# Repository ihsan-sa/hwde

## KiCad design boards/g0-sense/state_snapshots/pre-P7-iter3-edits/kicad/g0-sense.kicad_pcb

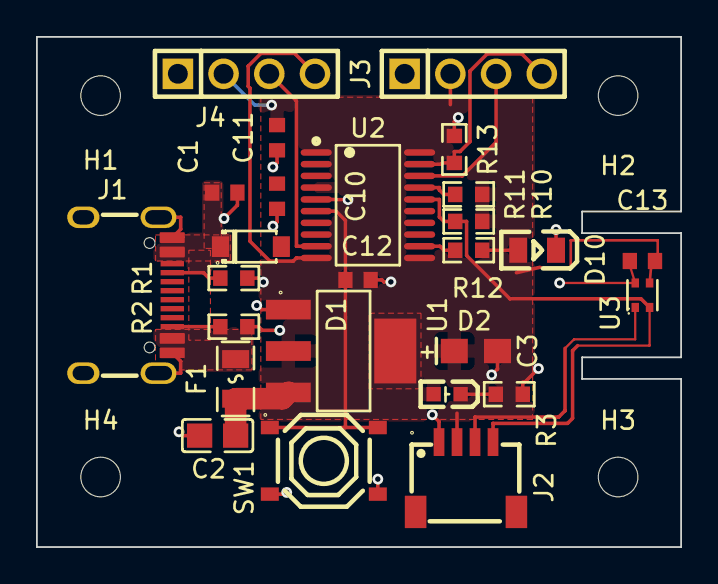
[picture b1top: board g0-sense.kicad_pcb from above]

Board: 2 copper layers, 35.8 x 28.3 mm, 30 parts (0 on the bottom side), 16 nets.

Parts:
C1, C10, C12, C13: 100nF 50V X7R; C0603
C2: 10uF 25V X5R; C0805
C3: 22uF 10V tantalum; CASE-A_3216
C11: 4.7uF 16V X5R; C0603
D1: SMF5.0A TVS 5V; SOD-123_L2.8-W1.8-LS3.7-RD
D2: Red LED; LED-SMD_L1.6-W0.8-R-RD
D10: Green 0805; LED0805-R-RD
F1: PTC 750mA 16V; F0805
H1, H2, H3, H4: MountingHole_2.2mm_M2
J1: TYPE-C-31-M-12; USB-C_SMD-TYPE-C-31-M-12_1
J2: Qwiic JST SH 4P; CONN-SMD_4P-P1.00_SM04B-SRSS-TB-LF-SN
J3, J4: 1x4 2.54mm THT (DNP); HDR-TH_4P-P2.54-V-M
R1, R2: 5.1k 1%; R0603
R3: 680R 1%; R0603
R10, R11: 1.5k; R0603
R12: 100R; R0603
R13: 10k; R0603
SW1: Tactile button; SW-SMD_4P-L5.1-W5.1-P3.70-LS6.5-TL_H1.5
U1: AMS1117-3.3; SOT-223-3_L6.5-W3.4-P2.30-LS7.0-BR
U2: STM32G030F6P6; TSSOP-20_L6.5-W4.4-P0.65-LS6.4-BL
U3: SHT40-AD1B-R2; DFN-4_L1.5-W1.5-P0.8-TL-EP

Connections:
+3V3: C3.1, C10.1, C11.1, C13.1, D2.1, J2.2, J3.2, J4.2, R10.2, R11.2, U1.2, U1.4, U2.4, U3.3
+5V: C2.1, F1.2, U1.3
/main/LED_A: D10.1, R12.2
/main/LED_USER: R12.1, U2.12
/main/NRST: C12.1, SW1.1, SW1.2, U2.6
/main/SCL: J2.4, R11.1, U2.16, U3.2
/main/SDA: J2.3, R10.1, U2.17, U3.1
/main/SWCLK: J3.4, R13.1, U2.19
/main/SWDIO: J3.3, U2.18
/main/UART_RX: J4.4, U2.10
/main/UART_TX: J4.3, U2.9
/power/CC1: J1.A5, R1.1
/power/CC2: J1.B5, R2.1
/power/PWR_LED_K: D2.2, R3.1
GND: C1.2, C2.2, C3.2, C10.2, C11.2, C12.2, C13.2, D1.2, D10.2, J1.1, J1.2, J1.3, J1.4, J1.A1B12, J1.B1A12, J2.1, J3.1, J4.1, R1.2, R2.2, R3.2, R13.2, SW1.3, SW1.4, U1.1, U2.5, U3.4
VBUS: C1.1, D1.1, F1.1, J1.A4B9, J1.B4A9

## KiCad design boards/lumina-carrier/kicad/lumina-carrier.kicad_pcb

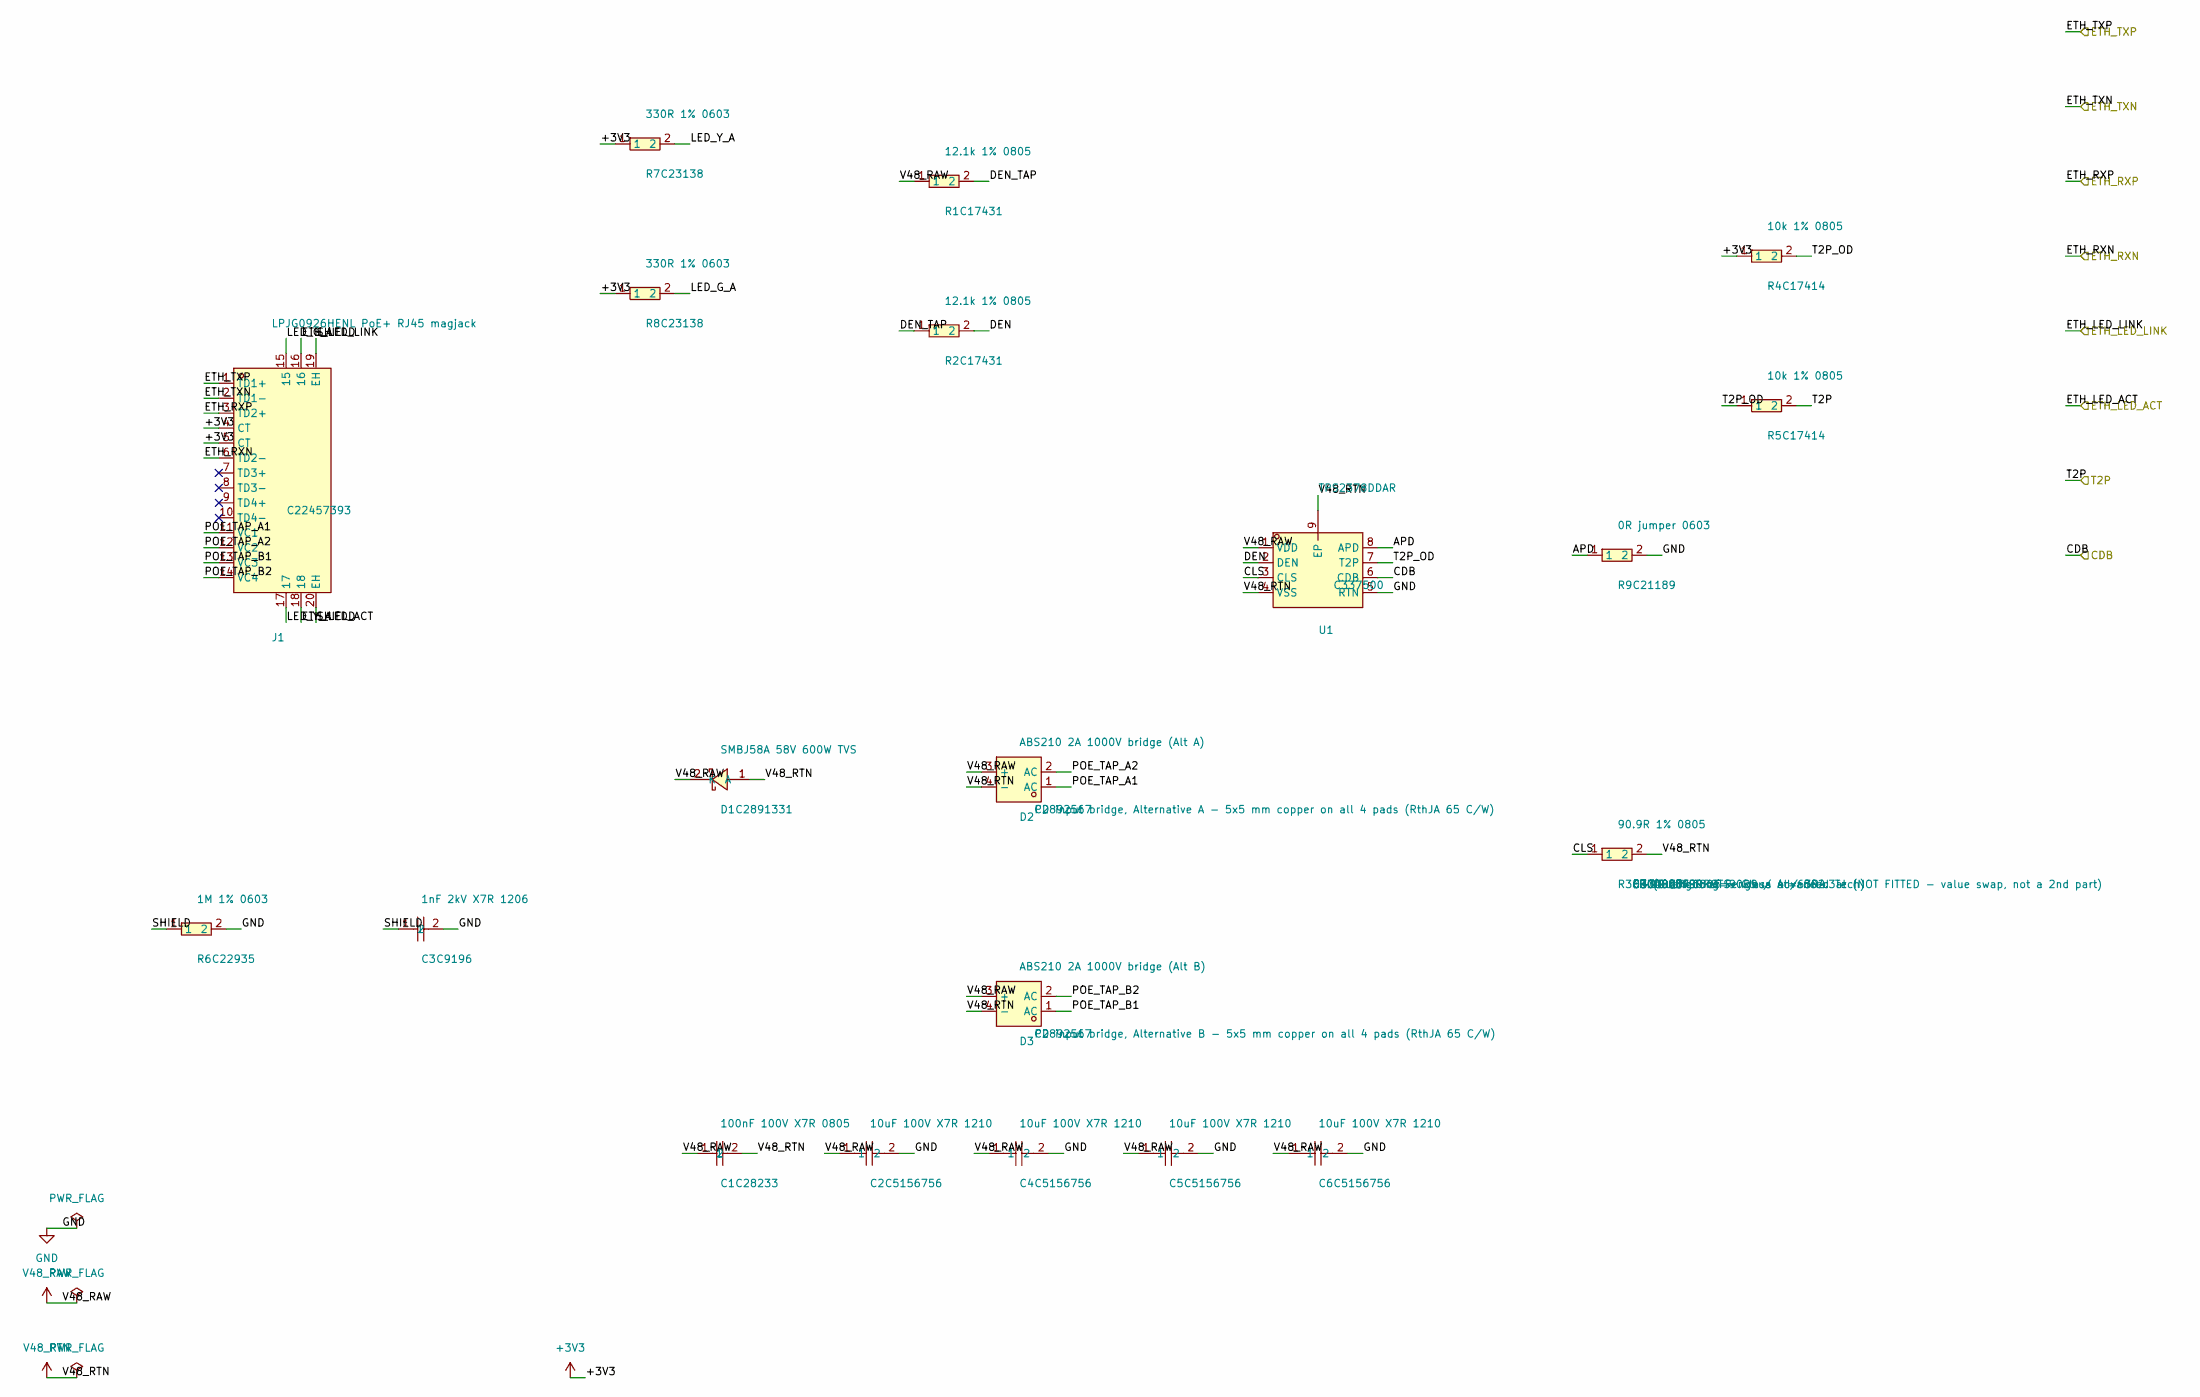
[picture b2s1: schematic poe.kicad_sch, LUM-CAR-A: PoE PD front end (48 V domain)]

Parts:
C1: 100nF 100V X7R 0805; C0805; LCSC C28233
C2, C4, C5, C6: 10uF 100V X7R 1210; C1210; LCSC C5156756
C3: 1nF 2kV X7R 1206; C1206; LCSC C9196
D1: SMBJ58A 58V 600W TVS; SMB_L4.3-W3.6-LS5.4-R-RD; LCSC C2891331
D2: ABS210 2A 1000V bridge (Alt A); ABF_L5.1-W4.4-P4.00-LS6.2-BL; LCSC C2892567
D3: ABS210 2A 1000V bridge (Alt B); ABF_L5.1-W4.4-P4.00-LS6.2-BL; LCSC C2892567
J1: LPJG0926HENL PoE+ RJ45 magjack; RJ45-TH_LPJG0926HENL_C22457393; LCSC C22457393
R1, R2: 12.1k 1% 0805; R0805; LCSC C17431
R3: 90.9R 1% 0805; R0805; MPN FRC0805F90R9TS; LCSC C3000584
R4, R5: 10k 1% 0805; R0805; LCSC C17414
R6: 1M 1% 0603; R0603; LCSC C22935
R7, R8: 330R 1% 0603; R0603; LCSC C23138
R9: 0R jumper 0603; R0603; LCSC C21189
U1: TPS2378DDAR; SOIC-8-1EP_3.9x4.9mm_P1.27mm_EP2.95x4.9mm_Mask2.71x3.4mm; LCSC C337500

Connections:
+3V3: J1.4 (CT), J1.5 (CT), R4.1, R7.1, R8.1; also elsewhere on the board
/CDB: U1.6 (CDB); also elsewhere on the board
/ETH_LED_ACT: J1.18; also elsewhere on the board
/ETH_LED_LINK: J1.16; also elsewhere on the board
/ETH_RXN: J1.6 (TD2-); also elsewhere on the board
/ETH_RXP: J1.3 (TD2+); also elsewhere on the board
/ETH_TXN: J1.2 (TD1-); also elsewhere on the board
/ETH_TXP: J1.1 (TD1+); also elsewhere on the board
/T2P: R5.2; also elsewhere on the board
/poe/APD: R9.1, U1.8 (APD)
/poe/CLS: R3.1, U1.3 (CLS)
/poe/DEN: R2.2, U1.2 (DEN)
/poe/DEN_TAP: R1.2, R2.1
/poe/LED_G_A: J1.15, R8.2
/poe/LED_Y_A: J1.17, R7.2
/poe/POE_TAP_A1: D2.1 (AC), J1.11 (VC1)
/poe/POE_TAP_A2: D2.2 (AC), J1.12 (VC2)
/poe/POE_TAP_B1: D3.1 (AC), J1.13 (VC3)
/poe/POE_TAP_B2: D3.2 (AC), J1.14 (VC4)
/poe/SHIELD: C3.1, J1.19 (EH), J1.20 (EH), R6.1
/poe/T2P_OD: R4.2, R5.1, U1.7 (T2P)
GND: C2.2, C3.2, C4.2, C5.2, C6.2, R6.2, R9.2, U1.5 (RTN); also elsewhere on the board
V48_RAW: C1.1, C2.1, C4.1, C5.1, C6.1, D1.2 (K), D2.3 (+), D3.3 (+), R1.1, U1.1 (VDD); also elsewhere on the board
V48_RTN: C1.2, D1.1 (A), D2.4 (-), D3.4 (-), R3.2, U1.4 (VSS), U1.9 (EP)

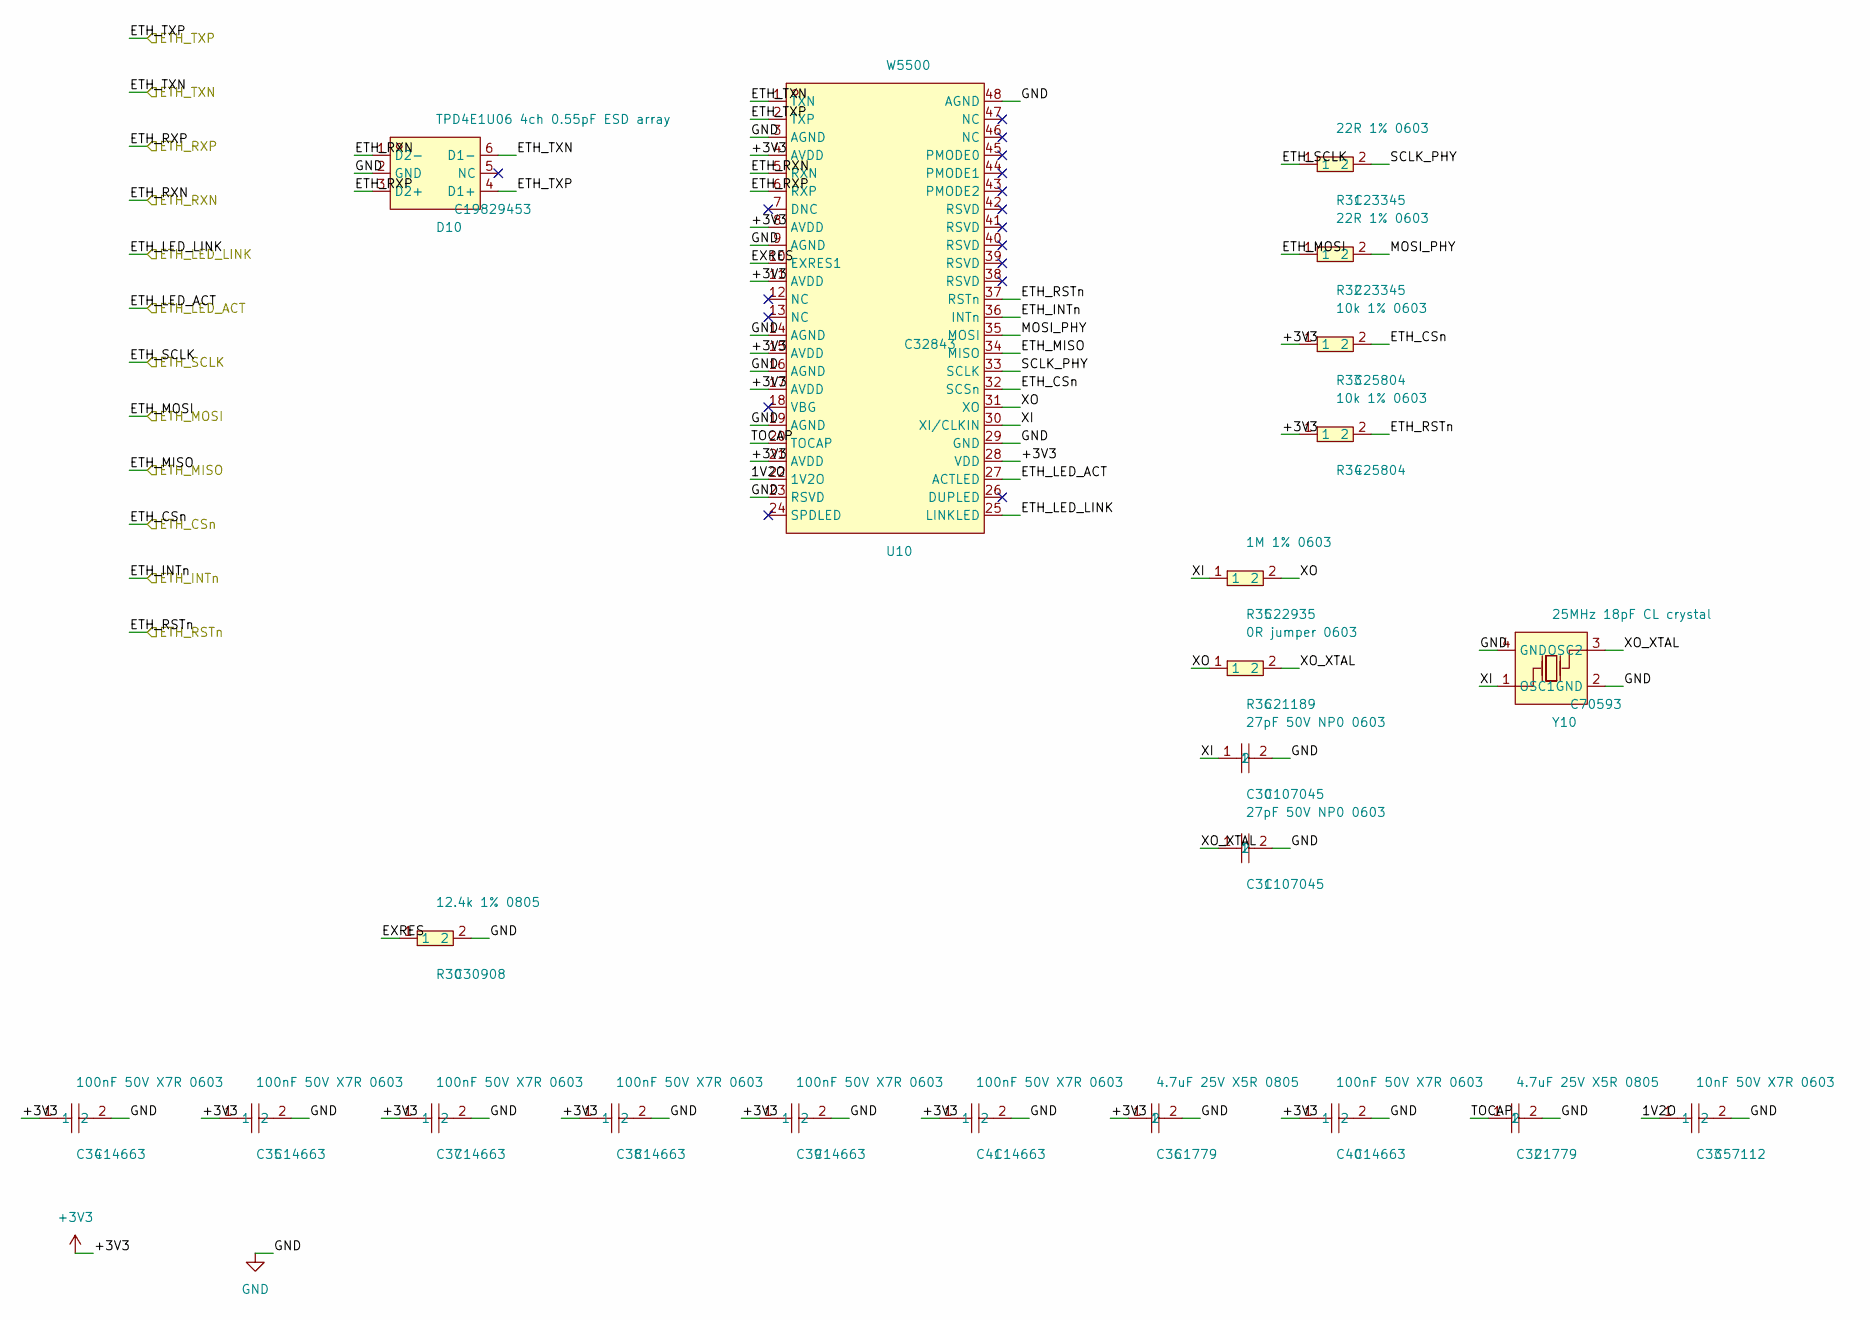
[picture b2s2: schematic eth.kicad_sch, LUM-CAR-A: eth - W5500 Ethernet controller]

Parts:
C30, C31: 27pF 50V NP0 0603; C0603; LCSC C107045
C32, C36: 4.7uF 25V X5R 0805; C0805; LCSC C1779
C33: 10nF 50V X7R 0603; C0603; LCSC C57112
C34, C35, C37, C38, C39, C40, C41: 100nF 50V X7R 0603; C0603; LCSC C14663
D10: TPD4E1U06 4ch 0.55pF ESD array; SOT-23-6_L2.9-W1.6-P0.95-LS2.8-BR; LCSC C19829453
R30: 12.4k 1% 0805; R0805; LCSC C30908
R31, R32: 22R 1% 0603; R0603; LCSC C23345
R33, R34: 10k 1% 0603; R0603; LCSC C25804
R35: 1M 1% 0603; R0603; LCSC C22935
R36: 0R jumper 0603; R0603; LCSC C21189
U10: W5500; LQFP-48_L7.0-W7.0-P0.50-LS9.0-BL; LCSC C32843
Y10: 25MHz 18pF CL crystal; OSC-SMD_4P-L3.2-W2.5-BL_SIT8008BI; LCSC C70593

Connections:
+3V3: C34.1, C35.1, C36.1, C37.1, C38.1, C39.1, C40.1, C41.1, R33.1, R34.1, U10.4 (AVDD), U10.8 (AVDD), U10.11 (AVDD), U10.15 (AVDD), U10.17 (AVDD), U10.21 (AVDD), U10.28 (VDD); also elsewhere on the board
/ETH_CSn: R33.2, U10.32 (SCSn); also elsewhere on the board
/ETH_INTn: U10.36 (INTn); also elsewhere on the board
/ETH_LED_ACT: U10.27 (ACTLED); also elsewhere on the board
/ETH_LED_LINK: U10.25 (LINKLED); also elsewhere on the board
/ETH_MISO: U10.34 (MISO); also elsewhere on the board
/ETH_MOSI: R32.1; also elsewhere on the board
/ETH_RSTn: R34.2, U10.37 (RSTn); also elsewhere on the board
/ETH_RXN: D10.1 (D2-), U10.5 (RXN); also elsewhere on the board
/ETH_RXP: D10.3 (D2+), U10.6 (RXP); also elsewhere on the board
/ETH_SCLK: R31.1; also elsewhere on the board
/ETH_TXN: D10.6 (D1-), U10.1 (TXN); also elsewhere on the board
/ETH_TXP: D10.4 (D1+), U10.2 (TXP); also elsewhere on the board
/eth/1V2O: C33.1, U10.22 (1V2O)
/eth/EXRES: R30.1, U10.10 (EXRES1)
/eth/MOSI_PHY: R32.2, U10.35 (MOSI)
/eth/SCLK_PHY: R31.2, U10.33 (SCLK)
/eth/TOCAP: C32.1, U10.20 (TOCAP)
/eth/XI: C30.1, R35.1, U10.30 (XI/CLKIN), Y10.1 (OSC1)
/eth/XO: R35.2, R36.1, U10.31 (XO)
/eth/XO_XTAL: C31.1, R36.2, Y10.3 (OSC2)
GND: C30.2, C31.2, C32.2, C33.2, C34.2, C35.2, C36.2, C37.2, C38.2, C39.2, C40.2, C41.2, D10.2 (GND), R30.2, U10.3 (AGND), U10.9 (AGND), U10.14 (AGND), U10.16 (AGND), U10.19 (AGND), U10.23 (RSVD), U10.29 (GND), U10.48 (AGND), Y10.2 (GND), Y10.4 (GND); also elsewhere on the board

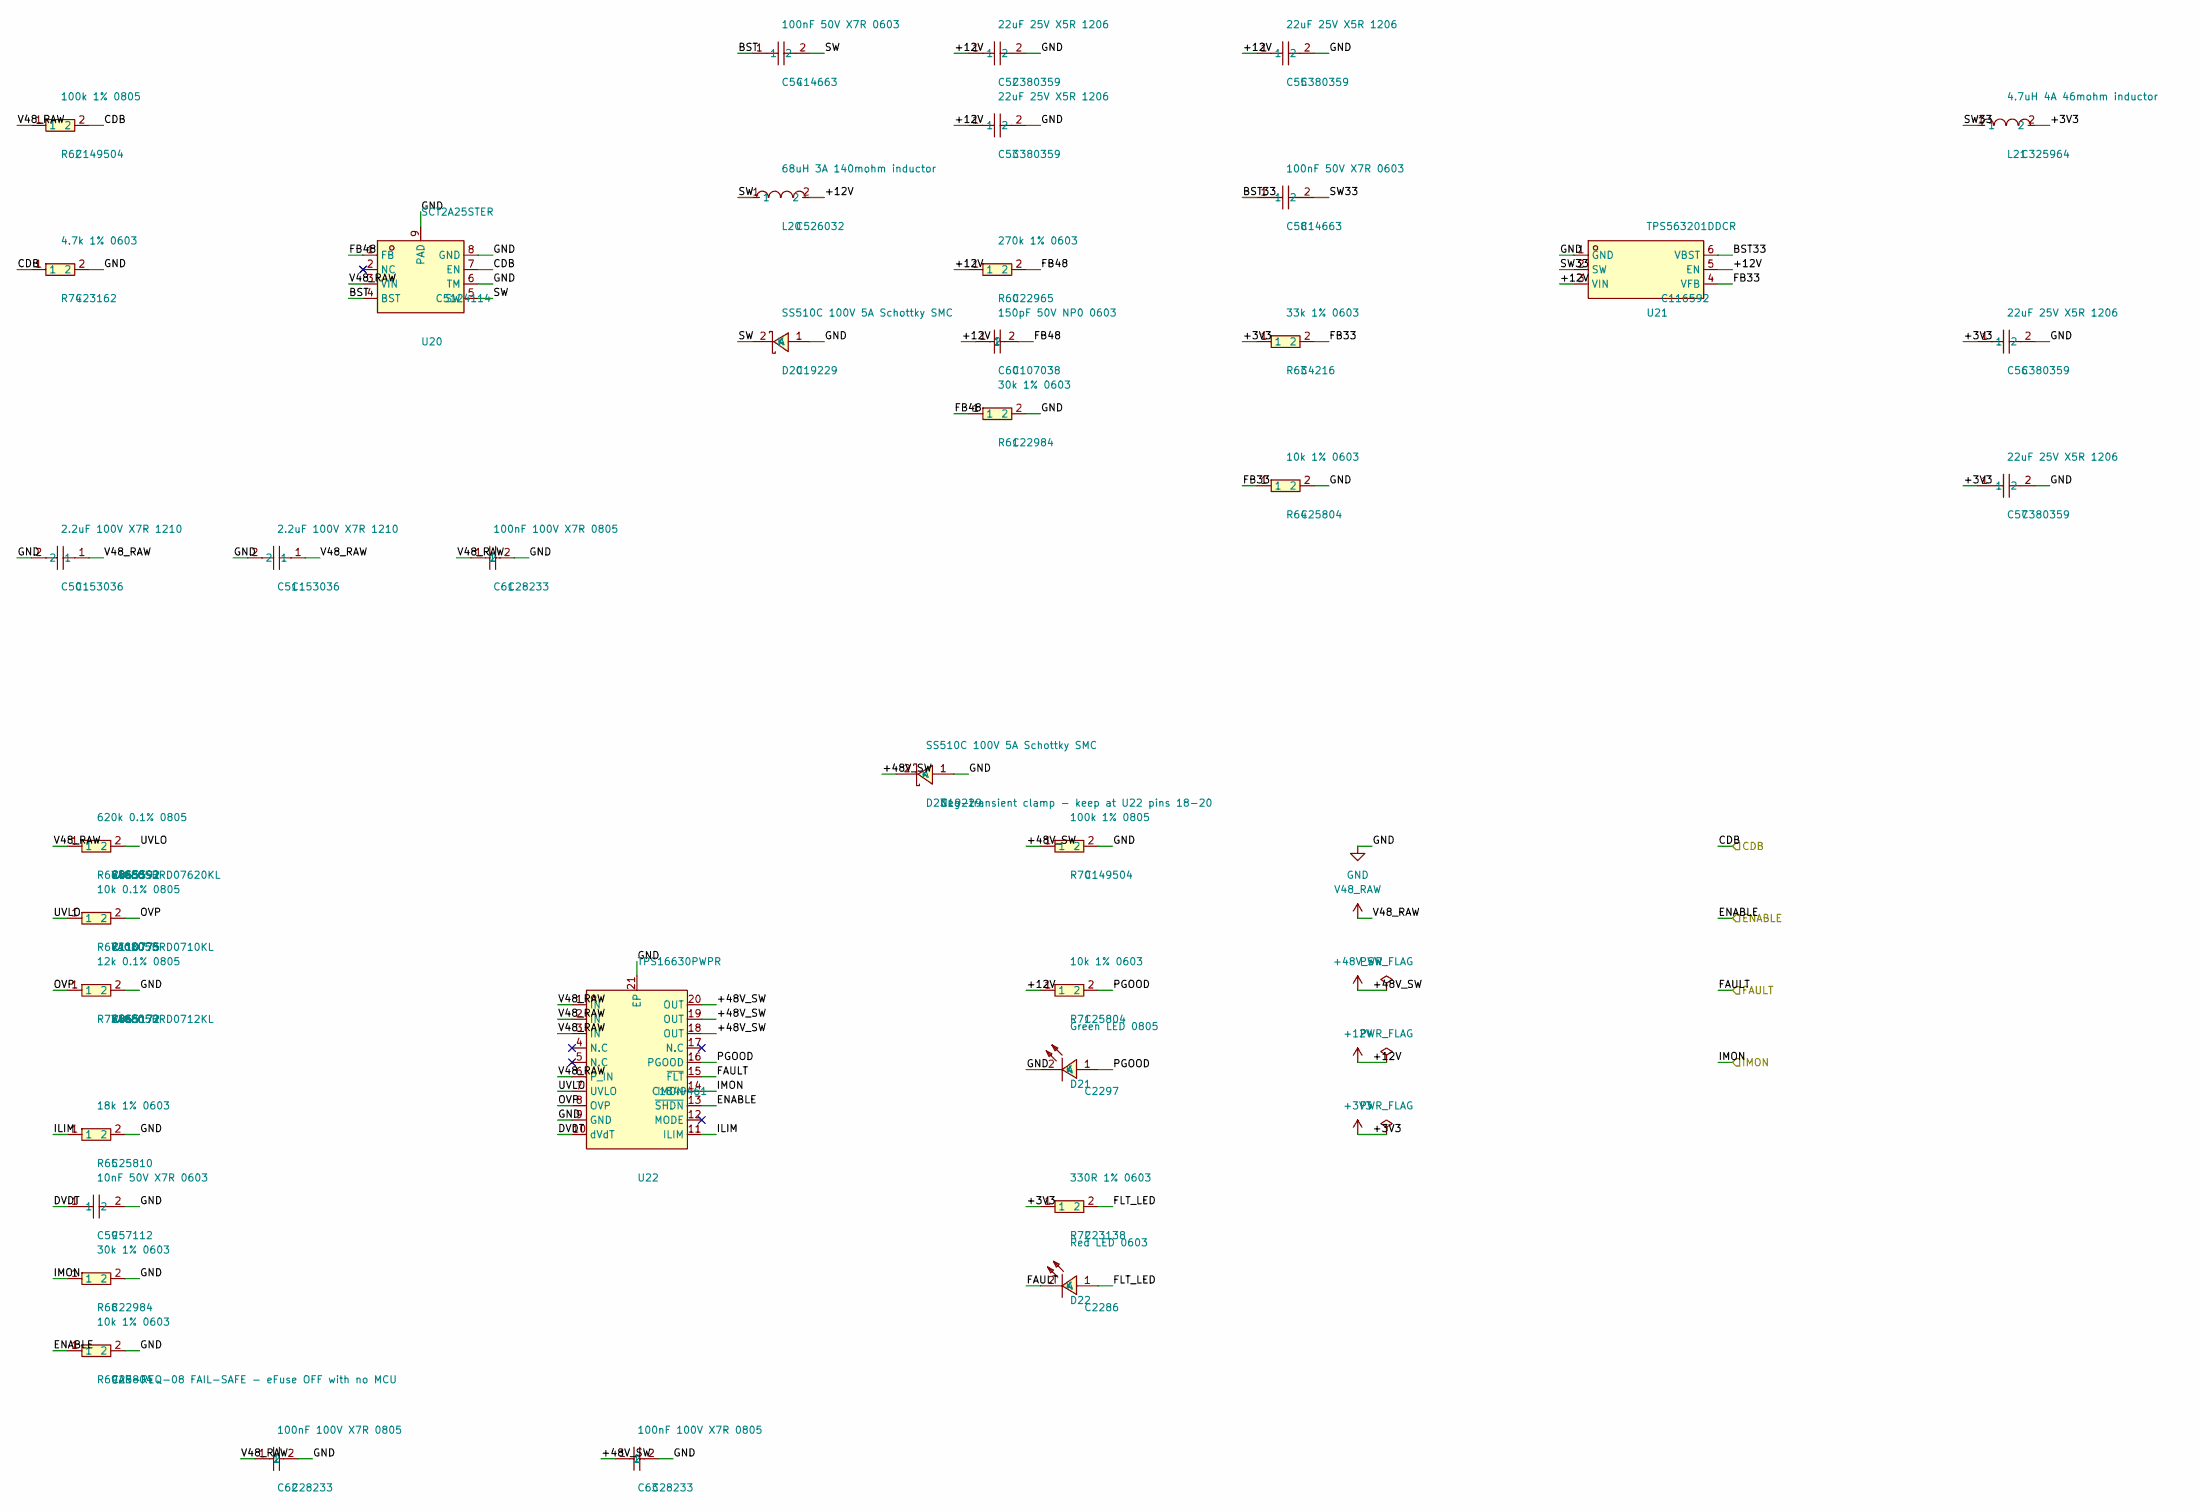
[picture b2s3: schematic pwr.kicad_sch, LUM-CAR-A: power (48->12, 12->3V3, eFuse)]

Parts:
C50, C51: 2.2uF 100V X7R 1210; C1210; LCSC C153036
C52, C53, C55, C56, C57: 22uF 25V X5R 1206; C1206; LCSC C380359
C54, C58: 100nF 50V X7R 0603; C0603; LCSC C14663
C59: 10nF 50V X7R 0603; C0603; LCSC C57112
C60: 150pF 50V NP0 0603; C0603; LCSC C107038
C61, C62, C63: 100nF 100V X7R 0805; C0805; LCSC C28233
D20, D23: SS510C 100V 5A Schottky SMC; SMC_L7.1-W6.2-LS8.1-R-RD; LCSC C19229
D21: Green LED 0805; LED0805-R-RD; LCSC C2297
D22: Red LED 0603; LED-SMD_L1.6-W0.8-R-RD; LCSC C2286
L20: 68uH 3A 140mohm inductor; IND-SMD_L12.6-W13.5; LCSC C526032
L21: 4.7uH 4A 46mohm inductor; IND-SMD_L5.4-W5.2; LCSC C325964
R60: 270k 1% 0603; R0603; LCSC C22965
R61, R68: 30k 1% 0603; R0603; LCSC C22984
R62, R70: 100k 1% 0805; R0805; LCSC C149504
R63: 33k 1% 0603; R0603; LCSC C4216
R64, R69, R71: 10k 1% 0603; R0603; LCSC C25804
R65: 18k 1% 0603; R0603; LCSC C25810
R66: 620k 0.1% 0805; R0805; MPN RT0805BRD07620KL; LCSC C865592
R67: 10k 0.1% 0805; R0805; MPN RT0805BRD0710KL; LCSC C110775
R72: 330R 1% 0603; R0603; LCSC C23138
R73: 12k 0.1% 0805; R0805; MPN RT0805BRD0712KL; LCSC C865172
R74: 4.7k 1% 0603; R0603; LCSC C23162
U20: SCT2A25STER; SOIC-8-1EP_3.9x4.9mm_P1.27mm_EP2.41x3.3mm; LCSC C5124114
U21: TPS563201DDCR; SOT-23-6_L2.9-W1.6-P0.95-LS2.8-BR; LCSC C116592
U22: TPS16630PWPR; HTSSOP-20-1EP_4.4x6.5mm_P0.65mm_EP3.4x6.5mm_Mask2.96x2.96mm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; LCSC C1849461

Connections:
+3V3: C56.1, C57.1, L21.2, R63.1, R72.1; also elsewhere on the board
+12V: C52.1, C53.1, C55.1, C60.1, L20.2, R60.1, R71.1, U21.3 (VIN), U21.5 (EN); also elsewhere on the board
+48V_SW: C63.1, D23.2 (K), R70.1, U22.18 (OUT), U22.19 (OUT), U22.20 (OUT); also elsewhere on the board
/CDB: R62.2, R74.1, U20.7 (EN); also elsewhere on the board
/ENABLE: R69.1, U22.13 (~SHDN); also elsewhere on the board
/FAULT: D22.2 (K), U22.15 (~FLT); also elsewhere on the board
/IMON: R68.1, U22.14 (IMON); also elsewhere on the board
/pwr/BST: C54.1, U20.4 (BST)
/pwr/BST33: C58.1, U21.6 (VBST)
/pwr/DVDT: C59.1, U22.10 (dVdT)
/pwr/FB33: R63.2, R64.1, U21.4 (VFB)
/pwr/FB48: C60.2, R60.2, R61.1, U20.1 (FB)
/pwr/FLT_LED: D22.1 (A), R72.2
/pwr/ILIM: R65.1, U22.11 (ILIM)
/pwr/OVP: R67.2, R73.1, U22.8 (OVP)
/pwr/PGOOD: D21.1 (A), R71.2, U22.16 (PGOOD)
/pwr/SW: C54.2, D20.2 (K), L20.1, U20.5 (SW)
/pwr/SW33: C58.2, L21.1, U21.2 (SW)
/pwr/UVLO: R66.2, R67.1, U22.7 (UVLO)
GND: C50.2, C51.2, C52.2, C53.2, C55.2, C56.2, C57.2, C59.2, C61.2, C62.2, C63.2, D20.1 (A), D21.2 (K), D23.1 (A), R61.2, R64.2, R65.2, R68.2, R69.2, R70.2, R73.2, R74.2, U20.6 (TM), U20.8 (GND), U20.9 (PAD), U21.1 (GND), U22.9 (GND), U22.21 (EP); also elsewhere on the board
V48_RAW: C50.1, C51.1, C61.1, C62.1, R62.1, R66.1, U20.3 (VIN), U22.1 (IN), U22.2 (IN), U22.3 (IN), U22.6 (P_IN); also elsewhere on the board

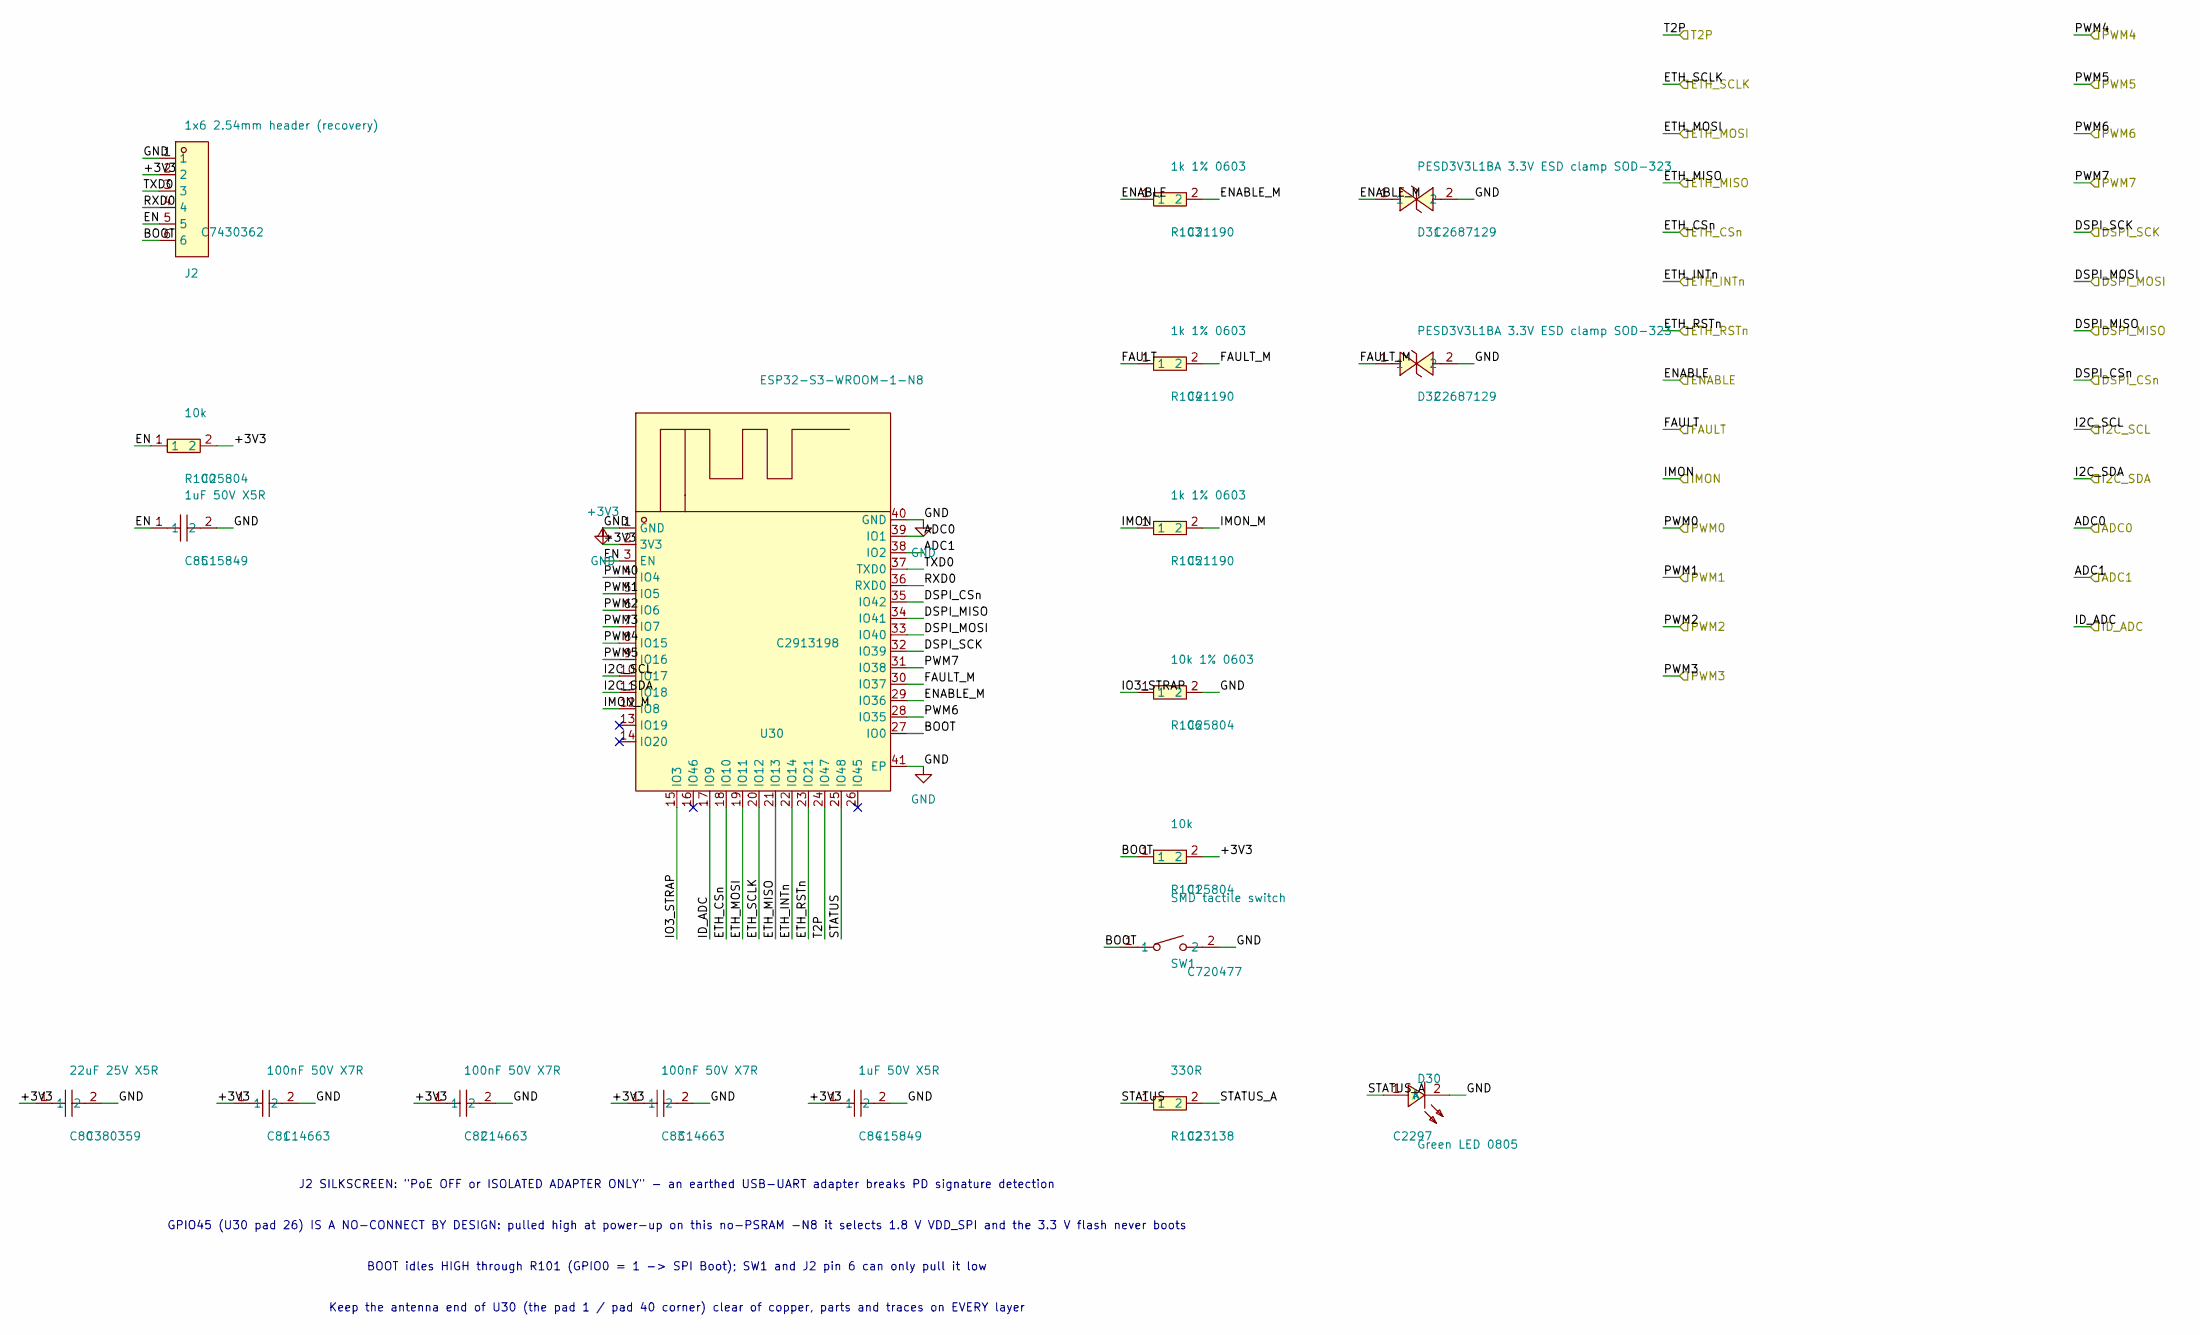
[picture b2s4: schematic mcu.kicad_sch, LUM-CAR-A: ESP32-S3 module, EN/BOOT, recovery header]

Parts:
C80: 22uF 25V X5R; C1206; LCSC C380359
C81, C82, C83: 100nF 50V X7R; C0603; LCSC C14663
C84, C85: 1uF 50V X5R; C0603; LCSC C15849
D30: Green LED 0805; LED0805-R-RD; LCSC C2297
D31, D32: PESD3V3L1BA 3.3V ESD clamp SOD-323; SOD-323_L1.7-W1.3-LS2.6-BI; LCSC C2687129
J2: 1x6 2.54mm header (recovery); CONN-TH_DS1021-1X6SF11-B; LCSC C7430362
R100, R101: 10k; R0603; LCSC C25804
R102: 330R; R0603; LCSC C23138
R103, R104, R105: 1k 1% 0603; R0603; LCSC C21190
R106: 10k 1% 0603; R0603; LCSC C25804
SW1: SMD tactile switch; SW-SMD_L3.9-W3.0-P4.45; LCSC C720477
U30: ESP32-S3-WROOM-1-N8; WIFIM-SMD_ESP32-S3-WROOM-1-N8; LCSC C2913198

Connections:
+3V3: C80.1, C81.1, C82.1, C83.1, C84.1, J2.2, R100.2, R101.2, U30.2 (3V3); also elsewhere on the board
/ADC0: U30.39 (IO1); also elsewhere on the board
/ADC1: U30.38 (IO2); also elsewhere on the board
/DSPI_CSn: U30.35 (IO42); also elsewhere on the board
/DSPI_MISO: U30.34 (IO41); also elsewhere on the board
/DSPI_MOSI: U30.33 (IO40); also elsewhere on the board
/DSPI_SCK: U30.32 (IO39); also elsewhere on the board
/ENABLE: R103.1; also elsewhere on the board
/ETH_CSn: U30.18 (IO10); also elsewhere on the board
/ETH_INTn: U30.22 (IO14); also elsewhere on the board
/ETH_MISO: U30.21 (IO13); also elsewhere on the board
/ETH_MOSI: U30.19 (IO11); also elsewhere on the board
/ETH_RSTn: U30.23 (IO21); also elsewhere on the board
/ETH_SCLK: U30.20 (IO12); also elsewhere on the board
/FAULT: R104.1; also elsewhere on the board
/I2C_SCL: U30.10 (IO17); also elsewhere on the board
/I2C_SDA: U30.11 (IO18); also elsewhere on the board
/ID_ADC: U30.17 (IO9); also elsewhere on the board
/IMON: R105.1; also elsewhere on the board
/PWM0: U30.4 (IO4); also elsewhere on the board
/PWM1: U30.5 (IO5); also elsewhere on the board
/PWM2: U30.6 (IO6); also elsewhere on the board
/PWM3: U30.7 (IO7); also elsewhere on the board
/PWM4: U30.8 (IO15); also elsewhere on the board
/PWM5: U30.9 (IO16); also elsewhere on the board
/PWM6: U30.28 (IO35); also elsewhere on the board
/PWM7: U30.31 (IO38); also elsewhere on the board
/T2P: U30.24 (IO47); also elsewhere on the board
/mcu/BOOT: J2.6, R101.1, SW1.1, U30.27 (IO0)
/mcu/EN: C85.1, J2.5, R100.1, U30.3 (EN)
/mcu/ENABLE_M: D31.1, R103.2, U30.29 (IO36)
/mcu/FAULT_M: D32.1, R104.2, U30.30 (IO37)
/mcu/IMON_M: R105.2, U30.12 (IO8)
/mcu/IO3_STRAP: R106.1, U30.15 (IO3)
/mcu/RXD0: J2.4, U30.36 (RXD0)
/mcu/STATUS: R102.1, U30.25 (IO48)
/mcu/STATUS_A: D30.1 (A), R102.2
/mcu/TXD0: J2.3, U30.37 (TXD0)
GND: C80.2, C81.2, C82.2, C83.2, C84.2, C85.2, D30.2 (K), D31.2, D32.2, J2.1, R106.2, SW1.2, U30.1 (GND), U30.40 (GND), U30.41 (EP); also elsewhere on the board

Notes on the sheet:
J2 SILKSCREEN: "PoE OFF or ISOLATED ADAPTER ONLY" - an earthed USB-UART adapter breaks PD signature detection
GPIO45 (U30 pad 26) IS A NO-CONNECT BY DESIGN: pulled high at power-up on this no-PSRAM -N8 it selects 1.8 V VDD_SPI and the 3.3 V flash never boots
BOOT idles HIGH through R101 (GPIO0 = 1 -> SPI Boot); SW1 and J2 pin 6 can only pull it low
Keep the antenna end of U30 (the pad 1 / pad 40 corner) clear of copper, parts and traces on EVERY layer

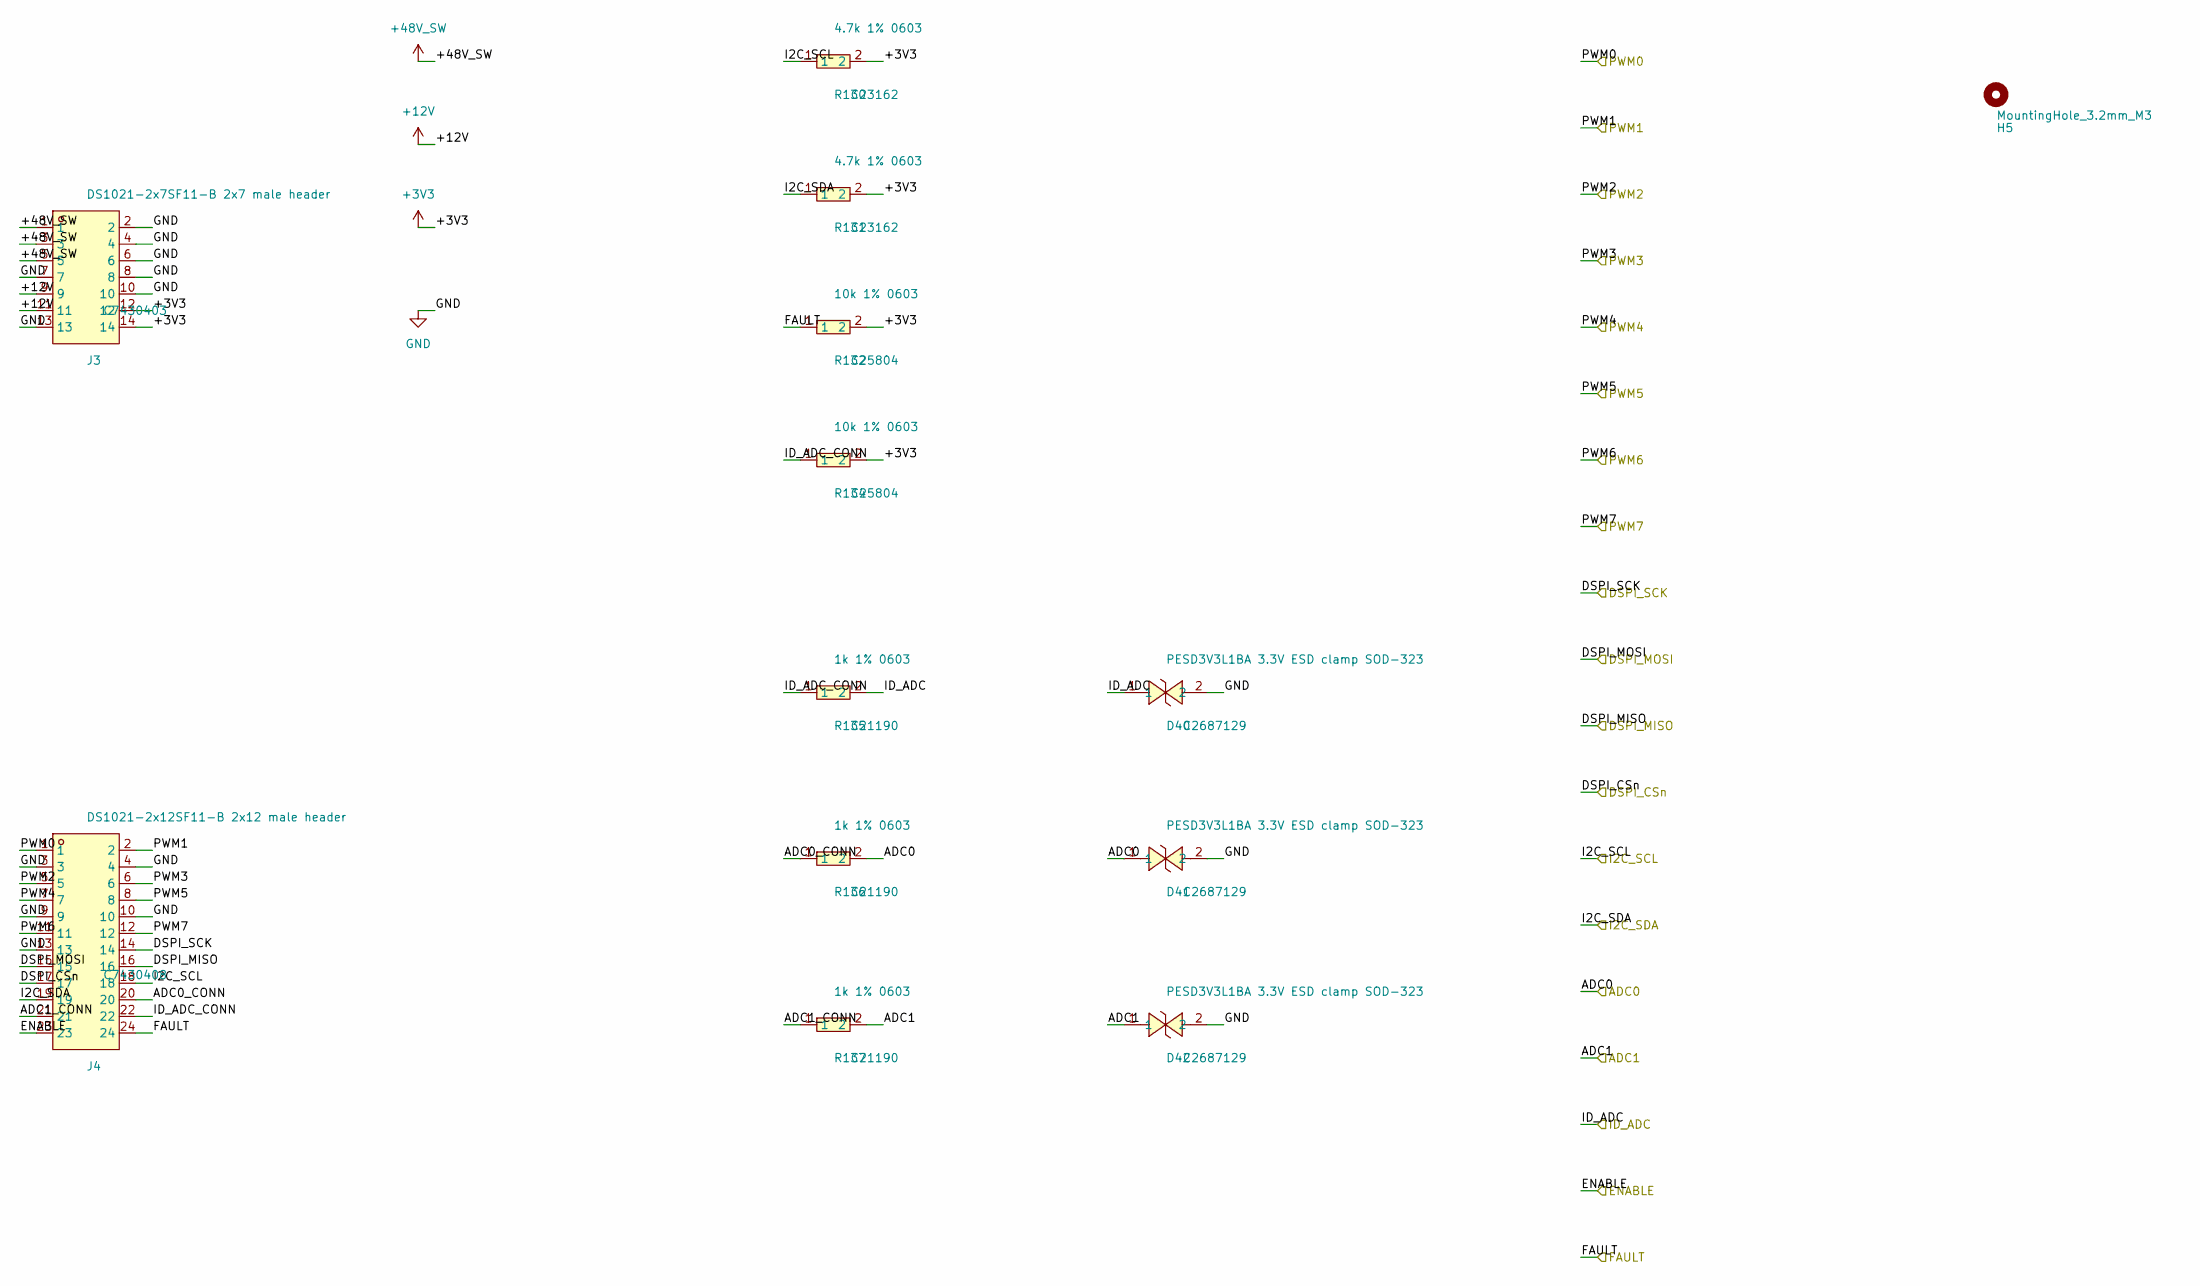
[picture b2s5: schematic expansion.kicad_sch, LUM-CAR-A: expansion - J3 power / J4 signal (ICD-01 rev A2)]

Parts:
D40, D41, D42: PESD3V3L1BA 3.3V ESD clamp SOD-323; SOD-323_L1.7-W1.3-LS2.6-BI; LCSC C2687129
H5: MountingHole_3.2mm_M3
J3: DS1021-2x7SF11-B 2x7 male header; HDR-TH_14P-P2.54-V-M-R2-C7-S2.54-1; LCSC C7430403
J4: DS1021-2x12SF11-B 2x12 male header; HDR-TH_24P-P2.54-V-M-R2-C12-S2.54; LCSC C7430408
R130, R131: 4.7k 1% 0603; R0603; LCSC C23162
R132, R134: 10k 1% 0603; R0603; LCSC C25804
R135, R136, R137: 1k 1% 0603; R0603; LCSC C21190

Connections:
+3V3: J3.12, J3.14, R130.2, R131.2, R132.2, R134.2; also elsewhere on the board
+12V: J3.9, J3.11; also elsewhere on the board
+48V_SW: J3.1, J3.3, J3.5; also elsewhere on the board
/ADC0: D41.1, R136.2; also elsewhere on the board
/ADC1: D42.1, R137.2; also elsewhere on the board
/DSPI_CSn: J4.17; also elsewhere on the board
/DSPI_MISO: J4.16; also elsewhere on the board
/DSPI_MOSI: J4.15; also elsewhere on the board
/DSPI_SCK: J4.14; also elsewhere on the board
/ENABLE: J4.23; also elsewhere on the board
/FAULT: J4.24, R132.1; also elsewhere on the board
/I2C_SCL: J4.18, R130.1; also elsewhere on the board
/I2C_SDA: J4.19, R131.1; also elsewhere on the board
/ID_ADC: D40.1, R135.2; also elsewhere on the board
/PWM0: J4.1; also elsewhere on the board
/PWM1: J4.2; also elsewhere on the board
/PWM2: J4.5; also elsewhere on the board
/PWM3: J4.6; also elsewhere on the board
/PWM4: J4.7; also elsewhere on the board
/PWM5: J4.8; also elsewhere on the board
/PWM6: J4.11; also elsewhere on the board
/PWM7: J4.12; also elsewhere on the board
/expansion/ADC0_CONN: J4.20, R136.1
/expansion/ADC1_CONN: J4.21, R137.1
/expansion/ID_ADC_CONN: J4.22, R134.1, R135.1
GND: D40.2, D41.2, D42.2, J3.2, J3.4, J3.6, J3.7, J3.8, J3.10, J3.13, J4.3, J4.4, J4.9, J4.10, J4.13; also elsewhere on the board
